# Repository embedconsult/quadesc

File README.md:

# BeagleConnect QuadESC

BeagleConnect QuadESC is a four-motor power board with BeagleConnect Torque installed as its system-on-module. This repository contains the editable mainboard and module designs, schematics, firmware sources and hardware manuals.

## Hardware documentation

The handoff manuals are maintained as Markdown in [`documentation/source/`](documentation/source/):

- [BeagleConnect QuadESC manual](documentation/source/quadesc/index.md): power, connections, sensing, control resources and mechanical integration.
- [BeagleConnect Torque product brief](documentation/source/som/product-brief.md): applications, features and design-backed specifications.
- [Word product brief](documentation/BeagleConnect-Torque-Features-and-Description.docx): complete specifications and board renders.
- [BeagleConnect Torque manual](documentation/source/som/index.md): module interfaces, pin assignments, power selection, TI BSL programming and debug.

Download the latest schematic PDFs generated from `main`:

- [BeagleConnect QuadESC schematic PDF](https://github.com/embedconsult/quadesc/releases/download/schematic-pdfs/mainboard_schematic.pdf)
- [BeagleConnect Torque schematic PDF](https://github.com/embedconsult/quadesc/releases/download/schematic-pdfs/som_schematic.pdf)

GitHub Actions publishes these files as assets of the rolling **Schematic PDFs** prerelease after revised schematics reach `main`. Pull requests provide downloadable preview artifacts. Generated PDFs are not stored in Git.

Connector references retain pin numbers, net names and electrical mappings. Use the KiCad designs for physical board geometry.

See [documentation build instructions](documentation/README.md) to generate the HTML site locally. CI builds and checks the same source for merge requests and pull requests, and publishes the manuals from `main` through GitHub Pages on [embedconsult/quadesc](https://github.com/embedconsult/quadesc), with an optional GitLab Pages pipeline for OpenBeagle. Generated HTML is a CI artifact rather than checked-in content.

## Repository layout

| Path | Contents |
| --- | --- |
| `mainboard/` | Editable BeagleConnect QuadESC mainboard design |
| `som/` | Editable BeagleConnect Torque module design |
| `documentation/source/` | Markdown manuals, shared diagrams and styling |
| `documentation/reference/` | Electrical connector, GPIO and analog reference data |
| `tools/documentation/` | Documentation build and validation scripts |
| `firmware/` | Firmware sources and existing application/loader artifacts |
| `drone-flasher-swd/` | SWD programming utility |

The **Schematic PDFs** GitHub Actions workflow rebuilds and publishes release assets after schematic changes. See [schematic PDF generation](tools/schematics/README.md) for pull-request previews, automatic updates on `main`, and local export instructions.

Documentation builds use only the manuals and their reference assets. See the [programming guide](documentation/source/som/firmware.md) for module programming interfaces.

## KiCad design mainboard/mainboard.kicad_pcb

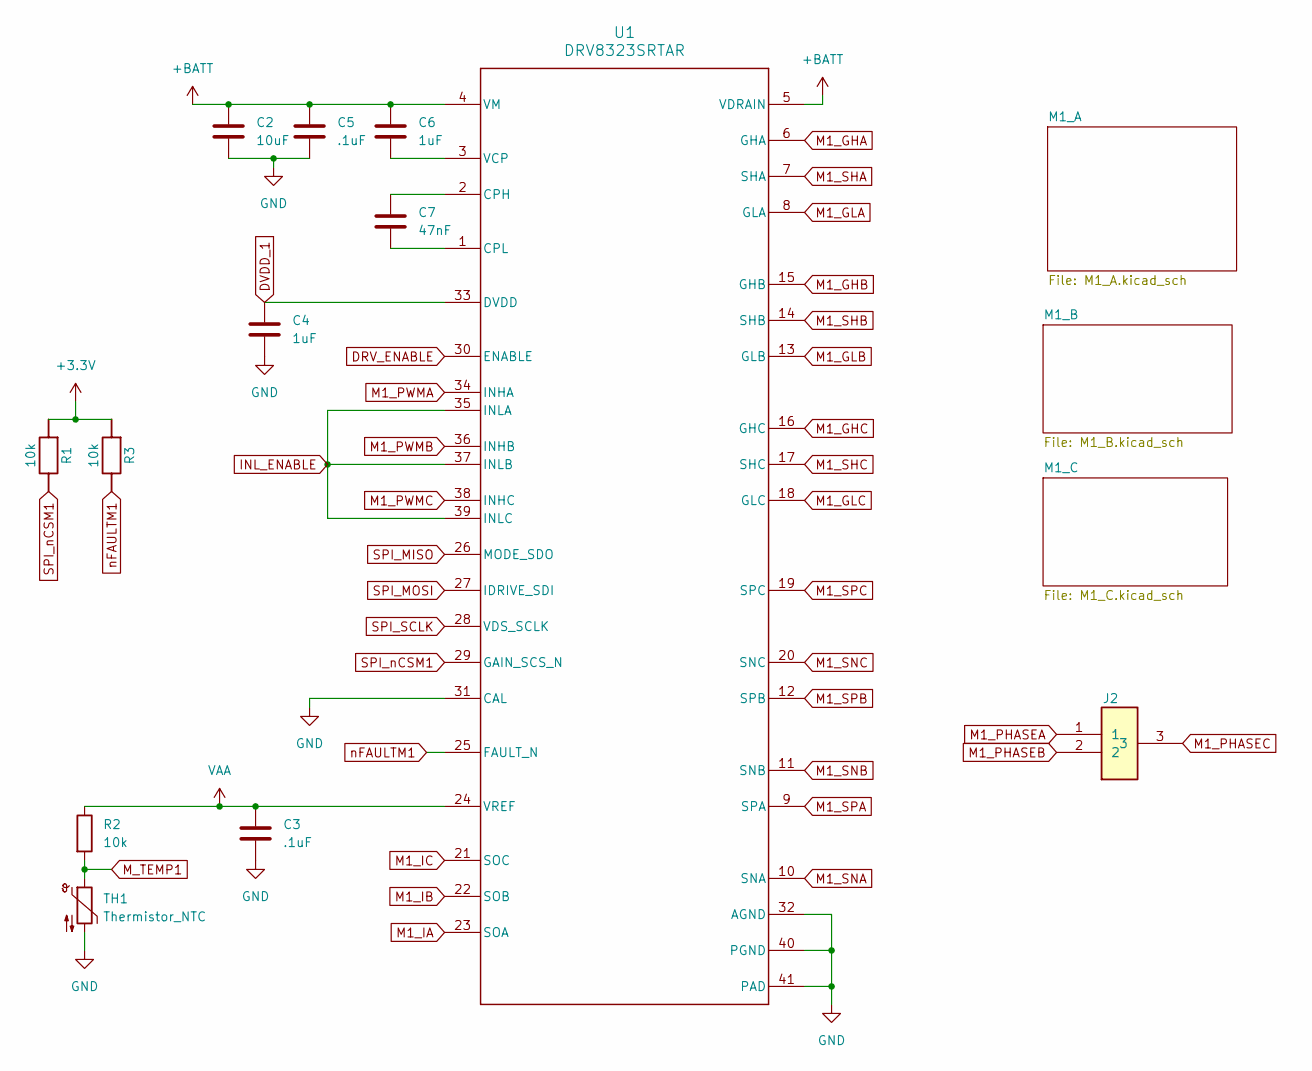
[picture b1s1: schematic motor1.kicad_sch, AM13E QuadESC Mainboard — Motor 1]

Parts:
C2: 10uF; C_1206_3216Metric
C3: .1uF; C_0201_0603Metric
C4: 1uF; C_0402_1005Metric
C5: .1uF; C_0402_1005Metric
C6: 1uF; C_0603_1608Metric
C7: 47nF; C_0402_1005Metric
J2: WirePad_Motor_3P_4.0x6.0_DualSide
R1, R2, R3: 10k; R_0201_0603Metric
TH1: Thermistor_NTC; R_0402_1005Metric
U1: DRV8323SRTAR; RTA0040B_NV

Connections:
+3.3V: R1.1, R3.1; also elsewhere on the board
+BATT: C2.1, C5.1, C6.1, U1.4 (VM), U1.5 (VDRAIN); also elsewhere on the board
DRV_ENABLE: U1.30 (ENABLE); also elsewhere on the board
DVDD_1: C4.1, U1.33 (DVDD)
GND: C2.2, C3.2, C4.2, C5.2, TH1.2, U1.31 (CAL), U1.32 (AGND), U1.40 (PGND), U1.41 (PAD); also elsewhere on the board
INL_ENABLE: U1.35 (INLA), U1.37 (INLB), U1.39 (INLC); also elsewhere on the board
M1_GHA: U1.6 (GHA); also elsewhere on the board
M1_GHB: U1.15 (GHB); also elsewhere on the board
M1_GHC: U1.16 (GHC); also elsewhere on the board
M1_GLA: U1.8 (GLA); also elsewhere on the board
M1_GLB: U1.13 (GLB); also elsewhere on the board
M1_GLC: U1.18 (GLC); also elsewhere on the board
M1_IA: U1.23 (SOA); also elsewhere on the board
M1_IB: U1.22 (SOB); also elsewhere on the board
M1_IC: U1.21 (SOC); also elsewhere on the board
M1_PHASEA: J2.1; also elsewhere on the board
M1_PHASEB: J2.2; also elsewhere on the board
M1_PHASEC: J2.3; also elsewhere on the board
M1_PWMA: U1.34 (INHA); also elsewhere on the board
M1_PWMB: U1.36 (INHB); also elsewhere on the board
M1_PWMC: U1.38 (INHC); also elsewhere on the board
M1_SHA: U1.7 (SHA); also elsewhere on the board
M1_SHB: U1.14 (SHB); also elsewhere on the board
M1_SHC: U1.17 (SHC); also elsewhere on the board
M1_SNA: U1.10 (SNA); also elsewhere on the board
M1_SNB: U1.11 (SNB); also elsewhere on the board
M1_SNC: U1.20 (SNC); also elsewhere on the board
M1_SPA: U1.9 (SPA); also elsewhere on the board
M1_SPB: U1.12 (SPB); also elsewhere on the board
M1_SPC: U1.19 (SPC); also elsewhere on the board
M_TEMP1: R2.2, TH1.1; also elsewhere on the board
unnamed: C7.1, U1.2 (CPH)
unnamed: C7.2, U1.1 (CPL)
unnamed: C6.2, U1.3 (VCP)
SPI_MISO: U1.26 (MODE_SDO); also elsewhere on the board
SPI_MOSI: U1.27 (IDRIVE_SDI); also elsewhere on the board
SPI_SCLK: U1.28 (VDS_SCLK); also elsewhere on the board
SPI_nCSM1: R1.2, U1.29 (GAIN_SCS_N); also elsewhere on the board
VAA: C3.1, R2.1, U1.24 (VREF); also elsewhere on the board
nFAULTM1: R3.2, U1.25 (FAULT_N); also elsewhere on the board

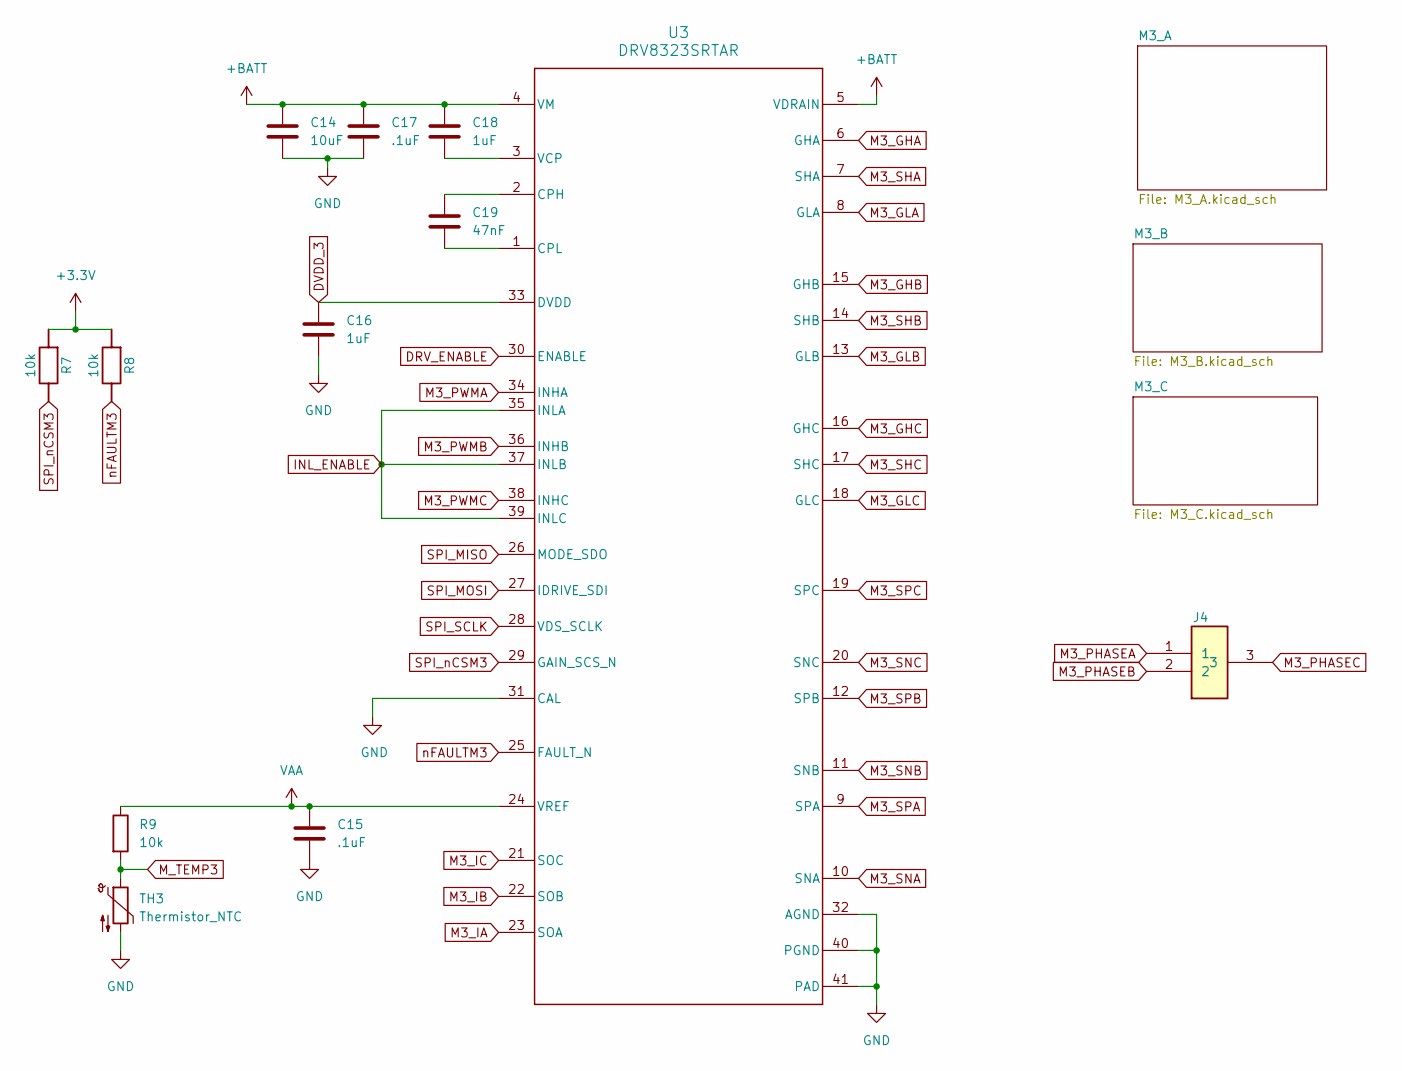
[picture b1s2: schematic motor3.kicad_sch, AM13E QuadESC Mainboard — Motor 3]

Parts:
C14: 10uF; C_1206_3216Metric
C15: .1uF; C_0201_0603Metric
C16: 1uF; C_0402_1005Metric
C17: .1uF; C_0402_1005Metric
C18: 1uF; C_0603_1608Metric
C19: 47nF; C_0402_1005Metric
J4: WirePad_Motor_3P_4.0x6.0_DualSide
R7, R8, R9: 10k; R_0201_0603Metric
TH3: Thermistor_NTC; R_0402_1005Metric
U3: DRV8323SRTAR; RTA0040B_NV

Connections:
+3.3V: R7.1, R8.1; also elsewhere on the board
+BATT: C14.1, C17.1, C18.1, U3.4 (VM), U3.5 (VDRAIN); also elsewhere on the board
DRV_ENABLE: U3.30 (ENABLE); also elsewhere on the board
DVDD_3: C16.1, U3.33 (DVDD)
GND: C14.2, C15.2, C16.2, C17.2, TH3.2, U3.31 (CAL), U3.32 (AGND), U3.40 (PGND), U3.41 (PAD); also elsewhere on the board
INL_ENABLE: U3.35 (INLA), U3.37 (INLB), U3.39 (INLC); also elsewhere on the board
M3_GHA: U3.6 (GHA); also elsewhere on the board
M3_GHB: U3.15 (GHB); also elsewhere on the board
M3_GHC: U3.16 (GHC); also elsewhere on the board
M3_GLA: U3.8 (GLA); also elsewhere on the board
M3_GLB: U3.13 (GLB); also elsewhere on the board
M3_GLC: U3.18 (GLC); also elsewhere on the board
M3_IA: U3.23 (SOA); also elsewhere on the board
M3_IB: U3.22 (SOB); also elsewhere on the board
M3_IC: U3.21 (SOC); also elsewhere on the board
M3_PHASEA: J4.1; also elsewhere on the board
M3_PHASEB: J4.2; also elsewhere on the board
M3_PHASEC: J4.3; also elsewhere on the board
M3_PWMA: U3.34 (INHA); also elsewhere on the board
M3_PWMB: U3.36 (INHB); also elsewhere on the board
M3_PWMC: U3.38 (INHC); also elsewhere on the board
M3_SHA: U3.7 (SHA); also elsewhere on the board
M3_SHB: U3.14 (SHB); also elsewhere on the board
M3_SHC: U3.17 (SHC); also elsewhere on the board
M3_SNA: U3.10 (SNA); also elsewhere on the board
M3_SNB: U3.11 (SNB); also elsewhere on the board
M3_SNC: U3.20 (SNC); also elsewhere on the board
M3_SPA: U3.9 (SPA); also elsewhere on the board
M3_SPB: U3.12 (SPB); also elsewhere on the board
M3_SPC: U3.19 (SPC); also elsewhere on the board
M_TEMP3: R9.2, TH3.1; also elsewhere on the board
unnamed: C19.1, U3.2 (CPH)
unnamed: C19.2, U3.1 (CPL)
unnamed: C18.2, U3.3 (VCP)
SPI_MISO: U3.26 (MODE_SDO); also elsewhere on the board
SPI_MOSI: U3.27 (IDRIVE_SDI); also elsewhere on the board
SPI_SCLK: U3.28 (VDS_SCLK); also elsewhere on the board
SPI_nCSM3: R7.2, U3.29 (GAIN_SCS_N); also elsewhere on the board
VAA: C15.1, R9.1, U3.24 (VREF); also elsewhere on the board
nFAULTM3: R8.2, U3.25 (FAULT_N); also elsewhere on the board

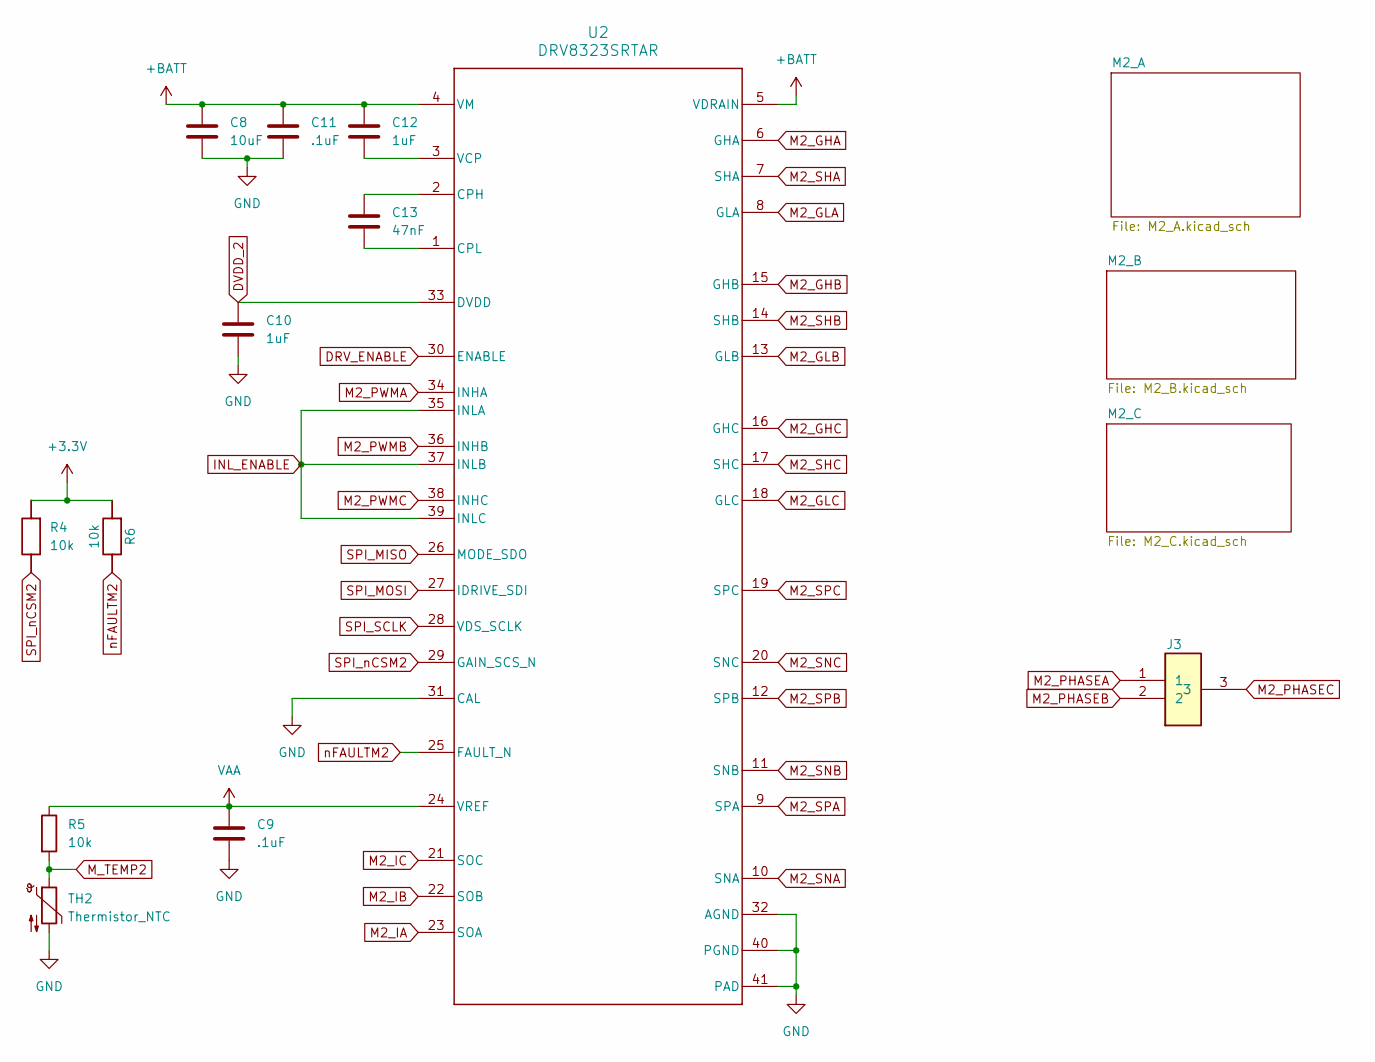
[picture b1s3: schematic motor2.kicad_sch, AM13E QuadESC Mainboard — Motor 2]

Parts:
C8: 10uF; C_1206_3216Metric
C9: .1uF; C_0201_0603Metric
C10: 1uF; C_0402_1005Metric
C11: .1uF; C_0402_1005Metric
C12: 1uF; C_0603_1608Metric
C13: 47nF; C_0402_1005Metric
J3: WirePad_Motor_3P_4.0x6.0_DualSide
R4, R5, R6: 10k; R_0201_0603Metric
TH2: Thermistor_NTC; R_0402_1005Metric
U2: DRV8323SRTAR; RTA0040B_NV

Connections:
+3.3V: R4.1, R6.1; also elsewhere on the board
+BATT: C8.1, C11.1, C12.1, U2.4 (VM), U2.5 (VDRAIN); also elsewhere on the board
DRV_ENABLE: U2.30 (ENABLE); also elsewhere on the board
DVDD_2: C10.1, U2.33 (DVDD)
GND: C8.2, C9.2, C10.2, C11.2, TH2.2, U2.31 (CAL), U2.32 (AGND), U2.40 (PGND), U2.41 (PAD); also elsewhere on the board
INL_ENABLE: U2.35 (INLA), U2.37 (INLB), U2.39 (INLC); also elsewhere on the board
M2_GHA: U2.6 (GHA); also elsewhere on the board
M2_GHB: U2.15 (GHB); also elsewhere on the board
M2_GHC: U2.16 (GHC); also elsewhere on the board
M2_GLA: U2.8 (GLA); also elsewhere on the board
M2_GLB: U2.13 (GLB); also elsewhere on the board
M2_GLC: U2.18 (GLC); also elsewhere on the board
M2_IA: U2.23 (SOA); also elsewhere on the board
M2_IB: U2.22 (SOB); also elsewhere on the board
M2_IC: U2.21 (SOC); also elsewhere on the board
M2_PHASEA: J3.1; also elsewhere on the board
M2_PHASEB: J3.2; also elsewhere on the board
M2_PHASEC: J3.3; also elsewhere on the board
M2_PWMA: U2.34 (INHA); also elsewhere on the board
M2_PWMB: U2.36 (INHB); also elsewhere on the board
M2_PWMC: U2.38 (INHC); also elsewhere on the board
M2_SHA: U2.7 (SHA); also elsewhere on the board
M2_SHB: U2.14 (SHB); also elsewhere on the board
M2_SHC: U2.17 (SHC); also elsewhere on the board
M2_SNA: U2.10 (SNA); also elsewhere on the board
M2_SNB: U2.11 (SNB); also elsewhere on the board
M2_SNC: U2.20 (SNC); also elsewhere on the board
M2_SPA: U2.9 (SPA); also elsewhere on the board
M2_SPB: U2.12 (SPB); also elsewhere on the board
M2_SPC: U2.19 (SPC); also elsewhere on the board
M_TEMP2: R5.2, TH2.1; also elsewhere on the board
unnamed: C13.1, U2.2 (CPH)
unnamed: C13.2, U2.1 (CPL)
unnamed: C12.2, U2.3 (VCP)
SPI_MISO: U2.26 (MODE_SDO); also elsewhere on the board
SPI_MOSI: U2.27 (IDRIVE_SDI); also elsewhere on the board
SPI_SCLK: U2.28 (VDS_SCLK); also elsewhere on the board
SPI_nCSM2: R4.2, U2.29 (GAIN_SCS_N); also elsewhere on the board
VAA: C9.1, R5.1, U2.24 (VREF); also elsewhere on the board
nFAULTM2: R6.2, U2.25 (FAULT_N); also elsewhere on the board

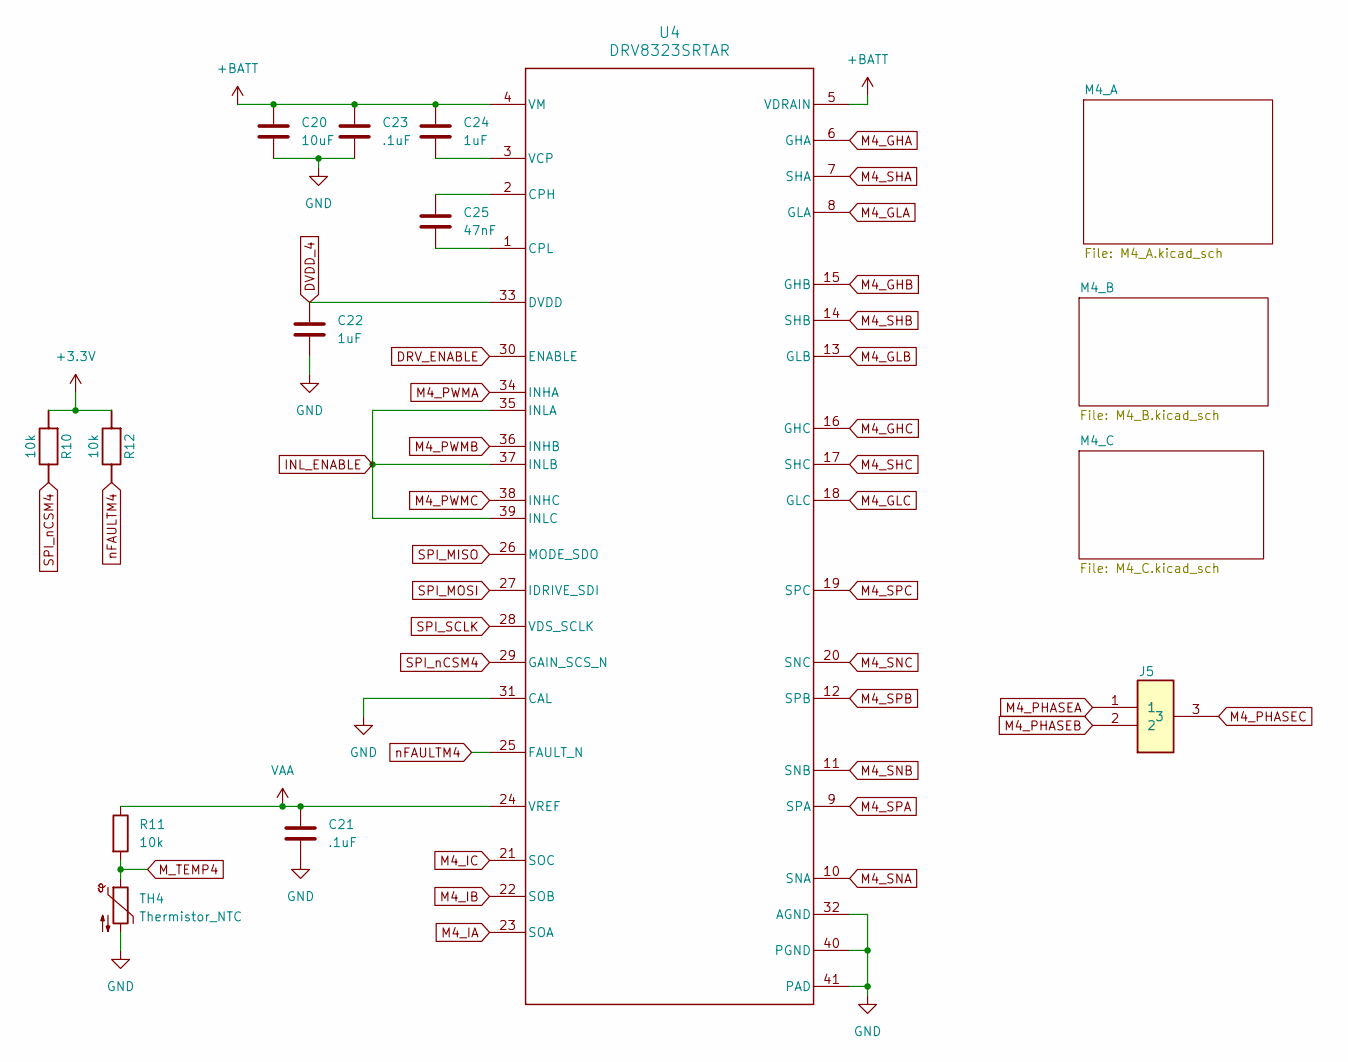
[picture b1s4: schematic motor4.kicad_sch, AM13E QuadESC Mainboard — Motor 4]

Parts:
C20: 10uF; C_1206_3216Metric
C21: .1uF; C_0201_0603Metric
C22: 1uF; C_0402_1005Metric
C23: .1uF; C_0402_1005Metric
C24: 1uF; C_0603_1608Metric
C25: 47nF; C_0402_1005Metric
J5: WirePad_Motor_3P_4.0x6.0_DualSide
R10, R11, R12: 10k; R_0201_0603Metric
TH4: Thermistor_NTC; R_0402_1005Metric
U4: DRV8323SRTAR; RTA0040B_NV

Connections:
+3.3V: R10.1, R12.1; also elsewhere on the board
+BATT: C20.1, C23.1, C24.1, U4.4 (VM), U4.5 (VDRAIN); also elsewhere on the board
DRV_ENABLE: U4.30 (ENABLE); also elsewhere on the board
DVDD_4: C22.1, U4.33 (DVDD)
GND: C20.2, C21.2, C22.2, C23.2, TH4.2, U4.31 (CAL), U4.32 (AGND), U4.40 (PGND), U4.41 (PAD); also elsewhere on the board
INL_ENABLE: U4.35 (INLA), U4.37 (INLB), U4.39 (INLC); also elsewhere on the board
M4_GHA: U4.6 (GHA); also elsewhere on the board
M4_GHB: U4.15 (GHB); also elsewhere on the board
M4_GHC: U4.16 (GHC); also elsewhere on the board
M4_GLA: U4.8 (GLA); also elsewhere on the board
M4_GLB: U4.13 (GLB); also elsewhere on the board
M4_GLC: U4.18 (GLC); also elsewhere on the board
M4_IA: U4.23 (SOA); also elsewhere on the board
M4_IB: U4.22 (SOB); also elsewhere on the board
M4_IC: U4.21 (SOC); also elsewhere on the board
M4_PHASEA: J5.1; also elsewhere on the board
M4_PHASEB: J5.2; also elsewhere on the board
M4_PHASEC: J5.3; also elsewhere on the board
M4_PWMA: U4.34 (INHA); also elsewhere on the board
M4_PWMB: U4.36 (INHB); also elsewhere on the board
M4_PWMC: U4.38 (INHC); also elsewhere on the board
M4_SHA: U4.7 (SHA); also elsewhere on the board
M4_SHB: U4.14 (SHB); also elsewhere on the board
M4_SHC: U4.17 (SHC); also elsewhere on the board
M4_SNA: U4.10 (SNA); also elsewhere on the board
M4_SNB: U4.11 (SNB); also elsewhere on the board
M4_SNC: U4.20 (SNC); also elsewhere on the board
M4_SPA: U4.9 (SPA); also elsewhere on the board
M4_SPB: U4.12 (SPB); also elsewhere on the board
M4_SPC: U4.19 (SPC); also elsewhere on the board
M_TEMP4: R11.2, TH4.1; also elsewhere on the board
unnamed: C25.1, U4.2 (CPH)
unnamed: C25.2, U4.1 (CPL)
unnamed: C24.2, U4.3 (VCP)
SPI_MISO: U4.26 (MODE_SDO); also elsewhere on the board
SPI_MOSI: U4.27 (IDRIVE_SDI); also elsewhere on the board
SPI_SCLK: U4.28 (VDS_SCLK); also elsewhere on the board
SPI_nCSM4: R10.2, U4.29 (GAIN_SCS_N); also elsewhere on the board
VAA: C21.1, R11.1, U4.24 (VREF); also elsewhere on the board
nFAULTM4: R12.2, U4.25 (FAULT_N); also elsewhere on the board

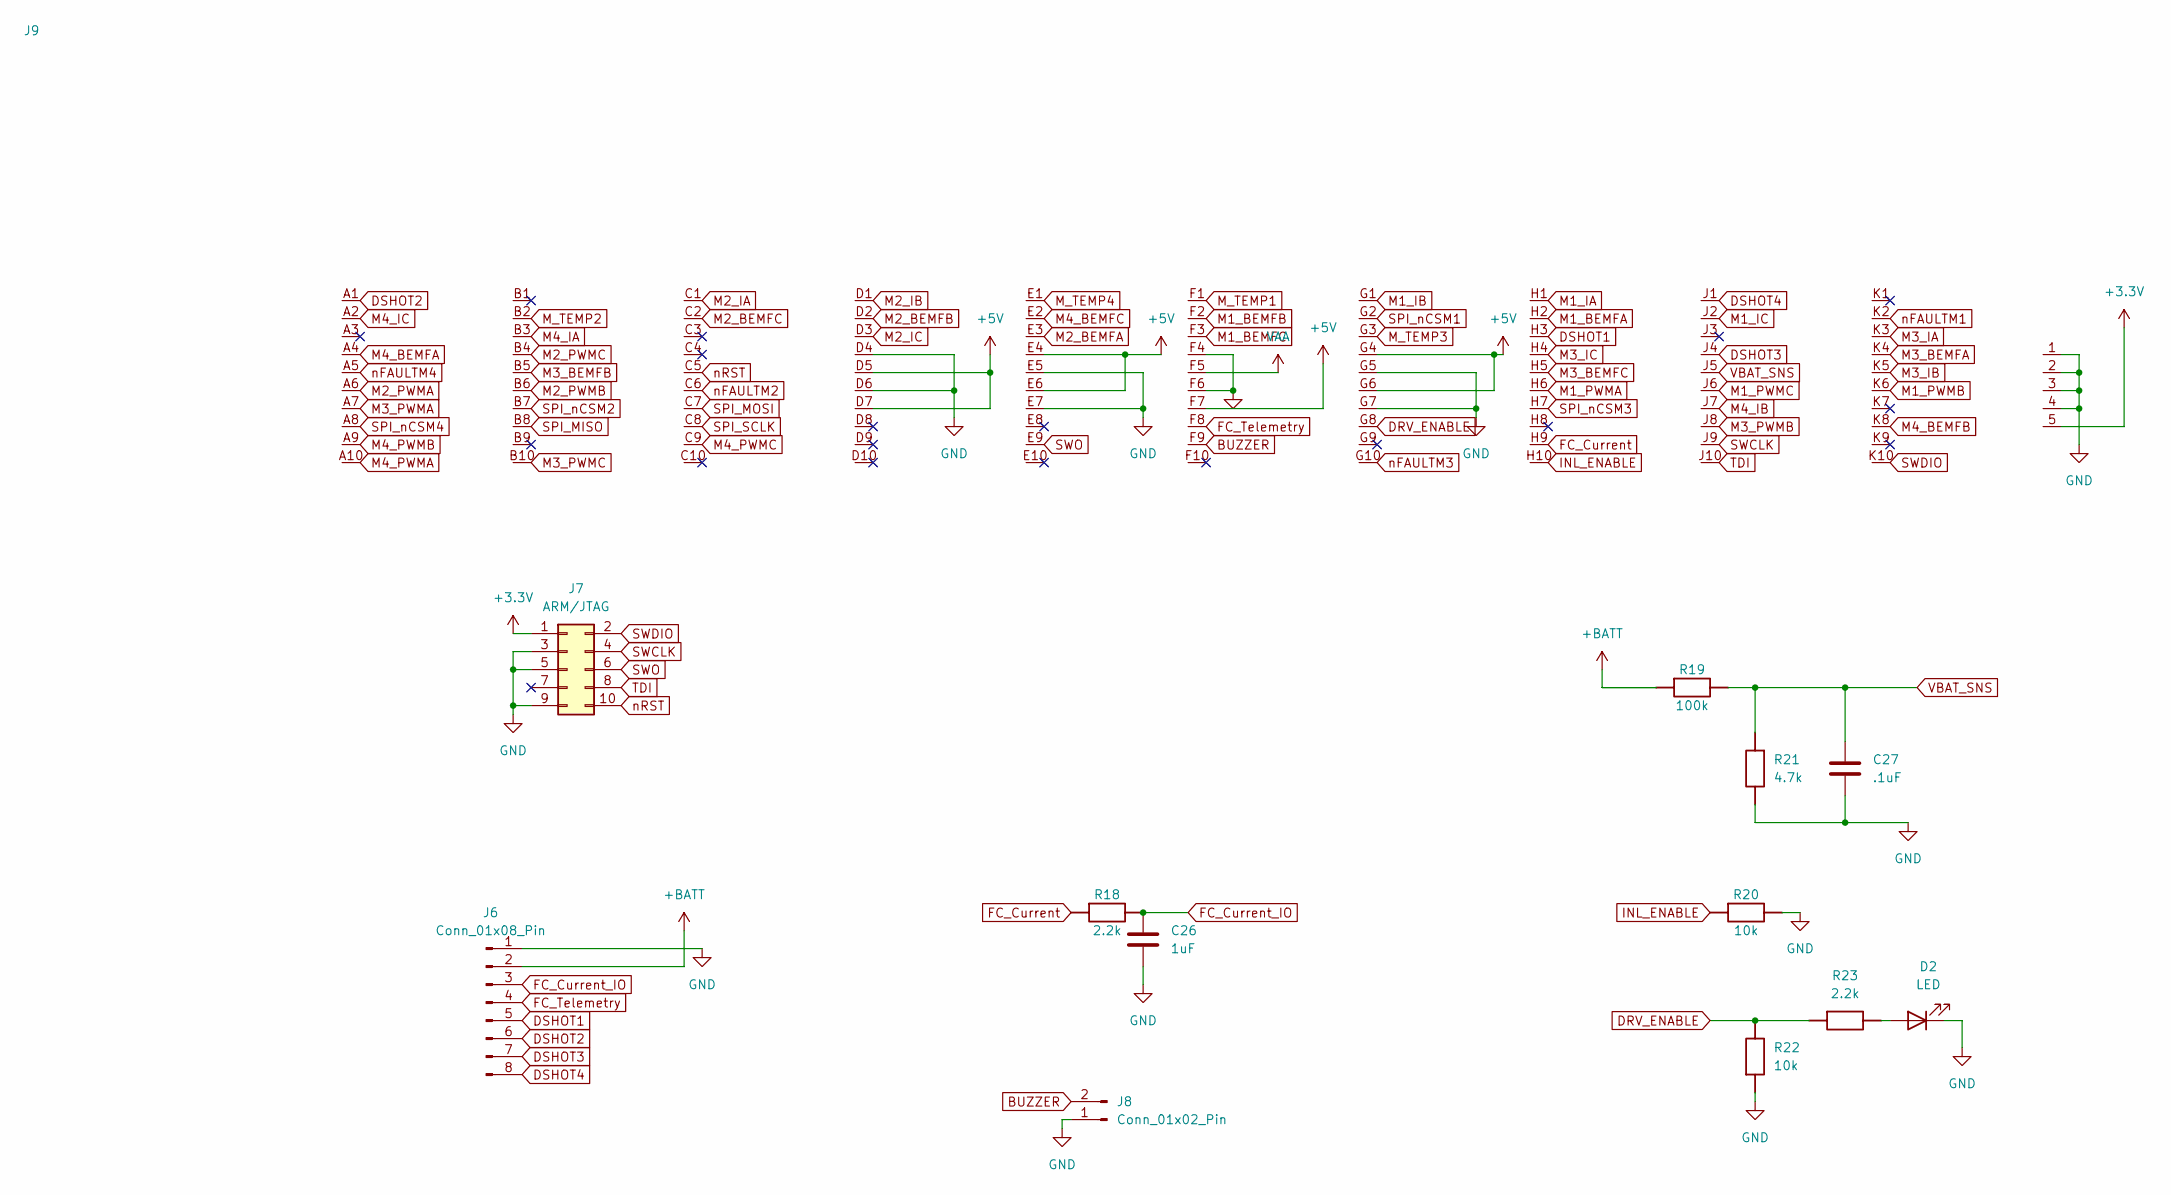
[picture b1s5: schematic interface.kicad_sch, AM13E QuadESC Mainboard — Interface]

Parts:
C26: 1uF; C_0402_1005Metric
C27: .1uF; C_0201_0603Metric
D2: LED; LED_0402_1005Metric
J6: Conn_01x08_Pin; JST_SM08B-SRSS-TB
J7: ARM/JTAG; PinHeader_2x05_P1.27mm_Vertical_SMD
J8: Conn_01x02_Pin; PinHeader_1x02_P1.00mm_Vertical
J9: AM13E_SoM_Receptacle_LGA100
R18, R23: 2.2k; R_0201_0603Metric
R19: 100k; R_0402_1005Metric
R20, R22: 10k; R_0201_0603Metric
R21: 4.7k; R_0201_0603Metric

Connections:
+3.3V: J7.1, J9.5; also elsewhere on the board
+BATT: J6.2, R19.1; also elsewhere on the board
BUCK_OUT: J9.D5, J9.D7, J9.E4, J9.E6, J9.F7, J9.G4, J9.G6; also elsewhere on the board
BUZZER: J8.2, J9.F9
DRV_ENABLE: J9.G8, R22.2, R23.1; also elsewhere on the board
DSHOT1: J6.5, J9.H3
DSHOT2: J6.6, J9.A1
DSHOT3: J6.7, J9.J4
DSHOT4: J6.8, J9.J1
FC_Current: J9.H9, R18.1
FC_Current_IO: C26.1, J6.3, R18.2
FC_Telemetry: J6.4, J9.F8
GND: C26.2, C27.2, D2.1 (K), J6.1, J7.3, J7.5, J7.9, J8.1, J9.1, J9.2, J9.3, J9.4, J9.D4, J9.D6, J9.E5, J9.E7, J9.F4, J9.F6, J9.G5, J9.G7, R20.2, R21.2, R22.1; also elsewhere on the board
INL_ENABLE: J9.H10, R20.1; also elsewhere on the board
M1_BEMFA: J9.H2; also elsewhere on the board
M1_BEMFB: J9.F2; also elsewhere on the board
M1_BEMFC: J9.F3; also elsewhere on the board
M1_IA: J9.H1; also elsewhere on the board
M1_IB: J9.G1; also elsewhere on the board
M1_IC: J9.J2; also elsewhere on the board
M1_PWMA: J9.H6; also elsewhere on the board
M1_PWMB: J9.K6; also elsewhere on the board
M1_PWMC: J9.J6; also elsewhere on the board
M2_BEMFA: J9.E3; also elsewhere on the board
M2_BEMFB: J9.D2; also elsewhere on the board
M2_BEMFC: J9.C2; also elsewhere on the board
M2_IA: J9.C1; also elsewhere on the board
M2_IB: J9.D1; also elsewhere on the board
M2_IC: J9.D3; also elsewhere on the board
M2_PWMA: J9.A6; also elsewhere on the board
M2_PWMB: J9.B6; also elsewhere on the board
M2_PWMC: J9.B4; also elsewhere on the board
M3_BEMFA: J9.K4; also elsewhere on the board
M3_BEMFB: J9.B5; also elsewhere on the board
M3_BEMFC: J9.H5; also elsewhere on the board
M3_IA: J9.K3; also elsewhere on the board
M3_IB: J9.K5; also elsewhere on the board
M3_IC: J9.H4; also elsewhere on the board
M3_PWMA: J9.A7; also elsewhere on the board
M3_PWMB: J9.J8; also elsewhere on the board
M3_PWMC: J9.B10; also elsewhere on the board
M4_BEMFA: J9.A4; also elsewhere on the board
M4_BEMFB: J9.K8; also elsewhere on the board
M4_BEMFC: J9.E2; also elsewhere on the board
M4_IA: J9.B3; also elsewhere on the board
M4_IB: J9.J7; also elsewhere on the board
M4_IC: J9.A2; also elsewhere on the board
M4_PWMA: J9.A10; also elsewhere on the board
M4_PWMB: J9.A9; also elsewhere on the board
M4_PWMC: J9.C9; also elsewhere on the board
M_TEMP1: J9.F1; also elsewhere on the board
M_TEMP2: J9.B2; also elsewhere on the board
M_TEMP3: J9.G3; also elsewhere on the board
M_TEMP4: J9.E1; also elsewhere on the board
unnamed: D2.2 (A), R23.2
SPI_MISO: J9.B8; also elsewhere on the board
SPI_MOSI: J9.C7; also elsewhere on the board
SPI_SCLK: J9.C8; also elsewhere on the board
SPI_nCSM1: J9.G2; also elsewhere on the board
SPI_nCSM2: J9.B7; also elsewhere on the board
SPI_nCSM3: J9.H7; also elsewhere on the board
SPI_nCSM4: J9.A8; also elsewhere on the board
SWCLK: J7.4, J9.J9
SWDIO: J7.2, J9.K10
SWO: J7.6, J9.E9
TDI: J7.8, J9.J10
VAA: J9.F5; also elsewhere on the board
VBAT_SNS: C27.1, J9.J5, R19.2, R21.1
nFAULTM1: J9.K2; also elsewhere on the board
nFAULTM2: J9.C6; also elsewhere on the board
nFAULTM3: J9.G10; also elsewhere on the board
nFAULTM4: J9.A5; also elsewhere on the board
nRST: J7.10, J9.C5

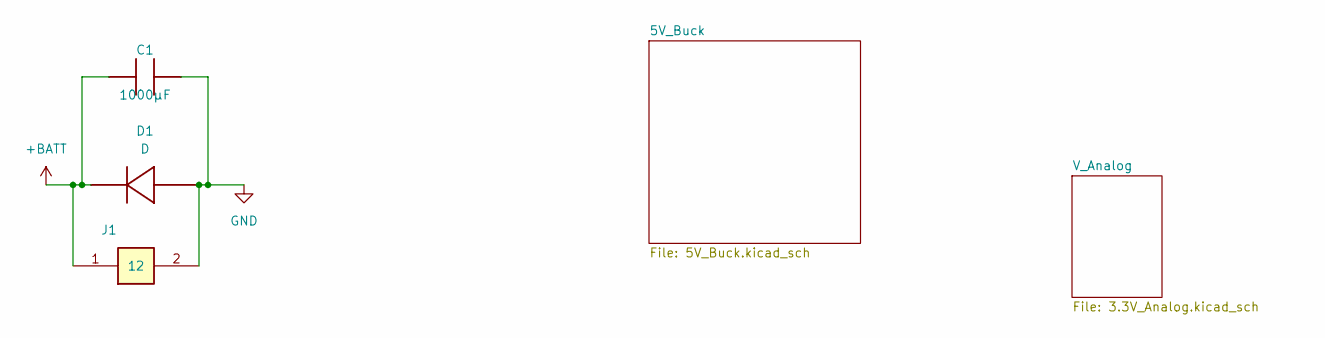
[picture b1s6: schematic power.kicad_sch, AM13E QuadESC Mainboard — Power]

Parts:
C1: 1000µF
D1: D; SMAJ26A
J1: WirePad_Battery_2P_5.0x9.0_DualSide

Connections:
+BATT: C1.1, D1.2, J1.1; also elsewhere on the board
GND: C1.2, D1.1, J1.2; also elsewhere on the board

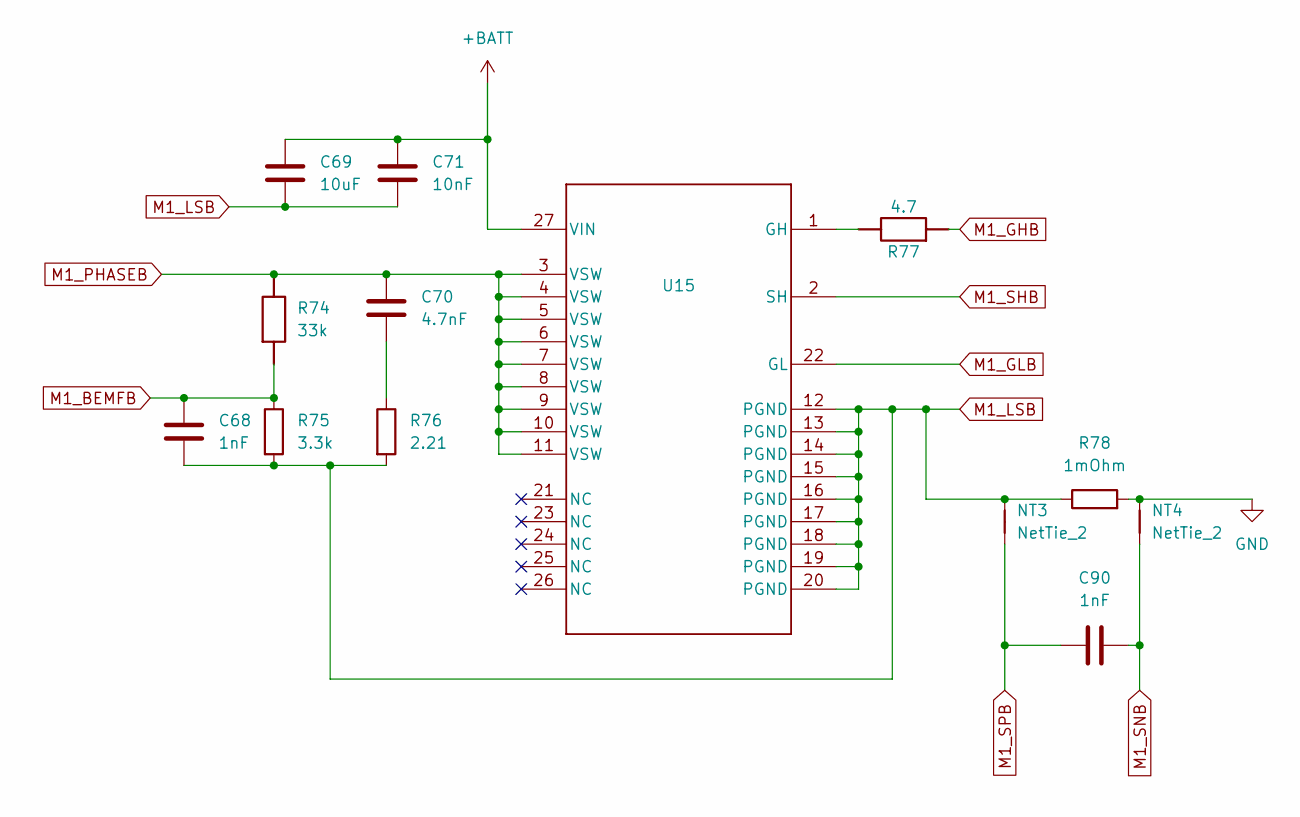
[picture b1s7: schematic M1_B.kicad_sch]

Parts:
C68, C90: 1nF; C_0201_0603Metric
C69: 10uF; C_1206_3216Metric
C70: 4.7nF; C_0402_1005Metric
C71: 10nF; C_0402_1005Metric
NT3, NT4: NetTie_2; NetTie-2_SMD_Pad0.2mm
R74: 33k; R_0402_1005Metric
R75: 3.3k; R_0201_0603Metric
R76: 2.21; R_0805_2012Metric
R77: 4.7; R_0402_1005Metric
R78: 1mOhm; RES_1L00x_BRN
U15: CSD88599Q5DC; DMM0022A

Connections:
+BATT: C69.1, C71.1, U15.27 (VIN); also elsewhere on the board
GND: NT4.2, R78.2; also elsewhere on the board
M1_BEMFB: C68.2, R74.1, R75.1; also elsewhere on the board
M1_GHB: R77.1; also elsewhere on the board
M1_GLB: U15.22 (GL); also elsewhere on the board
M1_LSB: C68.1, C69.2, C71.2, NT3.2, R75.2, R76.2, R78.1, U15.12 (PGND), U15.13 (PGND), U15.14 (PGND), U15.15 (PGND), U15.16 (PGND), U15.17 (PGND), U15.18 (PGND), U15.19 (PGND), U15.20 (PGND)
M1_PHASEB: C70.1, R74.2, U15.3 (VSW), U15.4 (VSW), U15.5 (VSW), U15.6 (VSW), U15.7 (VSW), U15.8 (VSW), U15.9 (VSW), U15.10 (VSW), U15.11 (VSW); also elsewhere on the board
M1_SHB: U15.2 (SH); also elsewhere on the board
M1_SNB: C90.2, NT4.1; also elsewhere on the board
M1_SPB: C90.1, NT3.1; also elsewhere on the board
unnamed: C70.2, R76.1
unnamed: R77.2, U15.1 (GH)

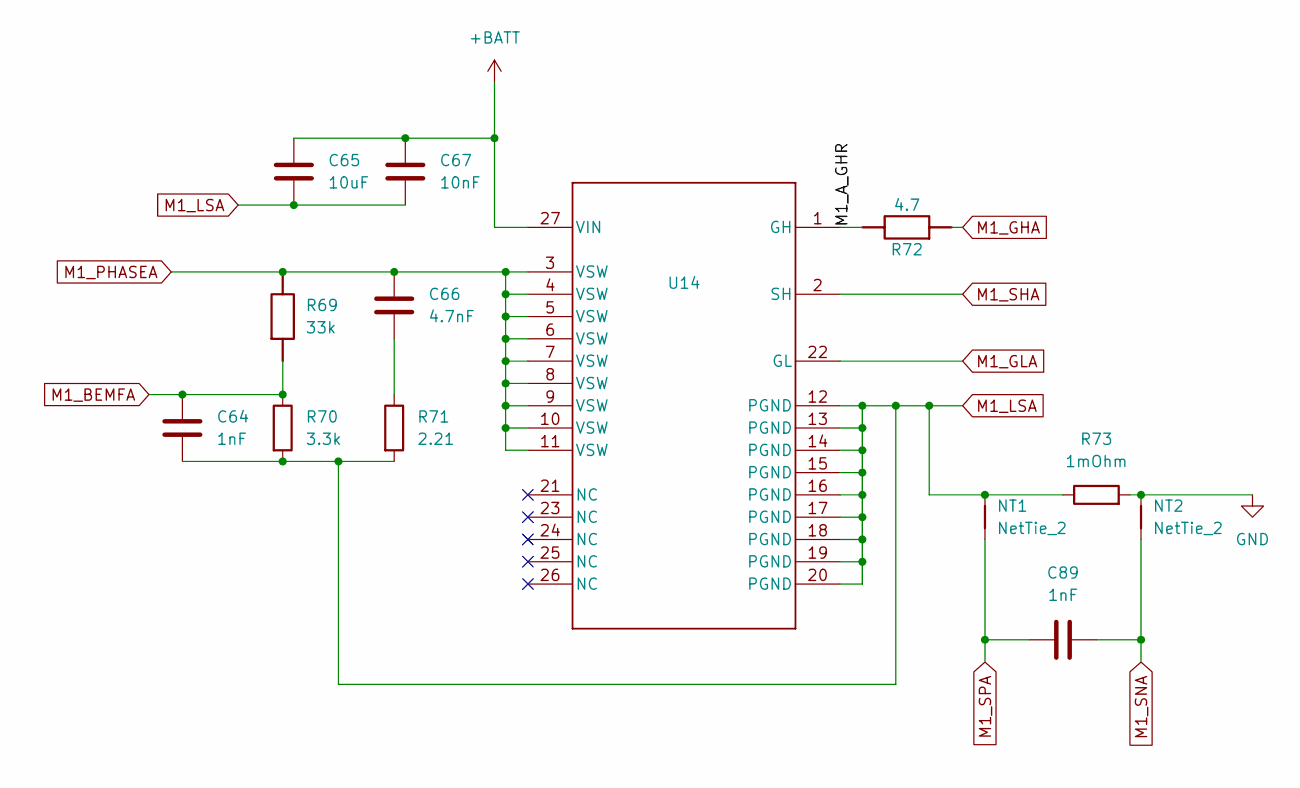
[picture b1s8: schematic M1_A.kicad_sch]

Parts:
C64, C89: 1nF; C_0201_0603Metric
C65: 10uF; C_1206_3216Metric
C66: 4.7nF; C_0402_1005Metric
C67: 10nF; C_0402_1005Metric
NT1, NT2: NetTie_2; NetTie-2_SMD_Pad0.2mm
R69: 33k; R_0402_1005Metric
R70: 3.3k; R_0201_0603Metric
R71: 2.21; R_0805_2012Metric
R72: 4.7; R_0402_1005Metric
R73: 1mOhm; RES_1L00x_BRN
U14: CSD88599Q5DC; DMM0022A

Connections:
+BATT: C65.1, C67.1, U14.27 (VIN); also elsewhere on the board
/M1/M1_A/M1_A_GHR: R72.2, U14.1 (GH)
GND: NT2.2, R73.2; also elsewhere on the board
M1_BEMFA: C64.2, R69.1, R70.1; also elsewhere on the board
M1_GHA: R72.1; also elsewhere on the board
M1_GLA: U14.22 (GL); also elsewhere on the board
M1_LSA: C64.1, C65.2, C67.2, NT1.2, R70.2, R71.2, R73.1, U14.12 (PGND), U14.13 (PGND), U14.14 (PGND), U14.15 (PGND), U14.16 (PGND), U14.17 (PGND), U14.18 (PGND), U14.19 (PGND), U14.20 (PGND)
M1_PHASEA: C66.1, R69.2, U14.3 (VSW), U14.4 (VSW), U14.5 (VSW), U14.6 (VSW), U14.7 (VSW), U14.8 (VSW), U14.9 (VSW), U14.10 (VSW), U14.11 (VSW); also elsewhere on the board
M1_SHA: U14.2 (SH); also elsewhere on the board
M1_SNA: C89.2, NT2.1; also elsewhere on the board
M1_SPA: C89.1, NT1.1; also elsewhere on the board
unnamed: C66.2, R71.1

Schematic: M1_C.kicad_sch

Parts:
C72, C91: 1nF; C_0201_0603Metric
C73: 10uF; C_1206_3216Metric
C74: 4.7nF; C_0402_1005Metric
C75: 10nF; C_0402_1005Metric
NT5, NT6: NetTie_2; NetTie-2_SMD_Pad0.2mm
R79: 33k; R_0402_1005Metric
R80: 3.3k; R_0201_0603Metric
R81: 2.21; R_0805_2012Metric
R82: 4.7; R_0402_1005Metric
R83: 1mOhm; RES_1L00x_BRN
U16: CSD88599Q5DC; DMM0022A

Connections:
+BATT: C73.1, C75.1, U16.27 (VIN); also elsewhere on the board
GND: NT6.2, R83.2; also elsewhere on the board
M1_BEMFC: C72.2, R79.1, R80.1; also elsewhere on the board
M1_GHC: R82.1; also elsewhere on the board
M1_GLC: U16.22 (GL); also elsewhere on the board
M1_LSC: C72.1, C73.2, C75.2, NT5.2, R80.2, R81.2, R83.1, U16.12 (PGND), U16.13 (PGND), U16.14 (PGND), U16.15 (PGND), U16.16 (PGND), U16.17 (PGND), U16.18 (PGND), U16.19 (PGND), U16.20 (PGND)
M1_PHASEC: C74.1, R79.2, U16.3 (VSW), U16.4 (VSW), U16.5 (VSW), U16.6 (VSW), U16.7 (VSW), U16.8 (VSW), U16.9 (VSW), U16.10 (VSW), U16.11 (VSW); also elsewhere on the board
M1_SHC: U16.2 (SH); also elsewhere on the board
M1_SNC: C91.2, NT6.1; also elsewhere on the board
M1_SPC: C91.1, NT5.1; also elsewhere on the board
unnamed: C74.2, R81.1
unnamed: R82.2, U16.1 (GH)
